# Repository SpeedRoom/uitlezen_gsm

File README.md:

Testcode voor het aansturen van de TFT dispalys die zullen dienen als gsm's.

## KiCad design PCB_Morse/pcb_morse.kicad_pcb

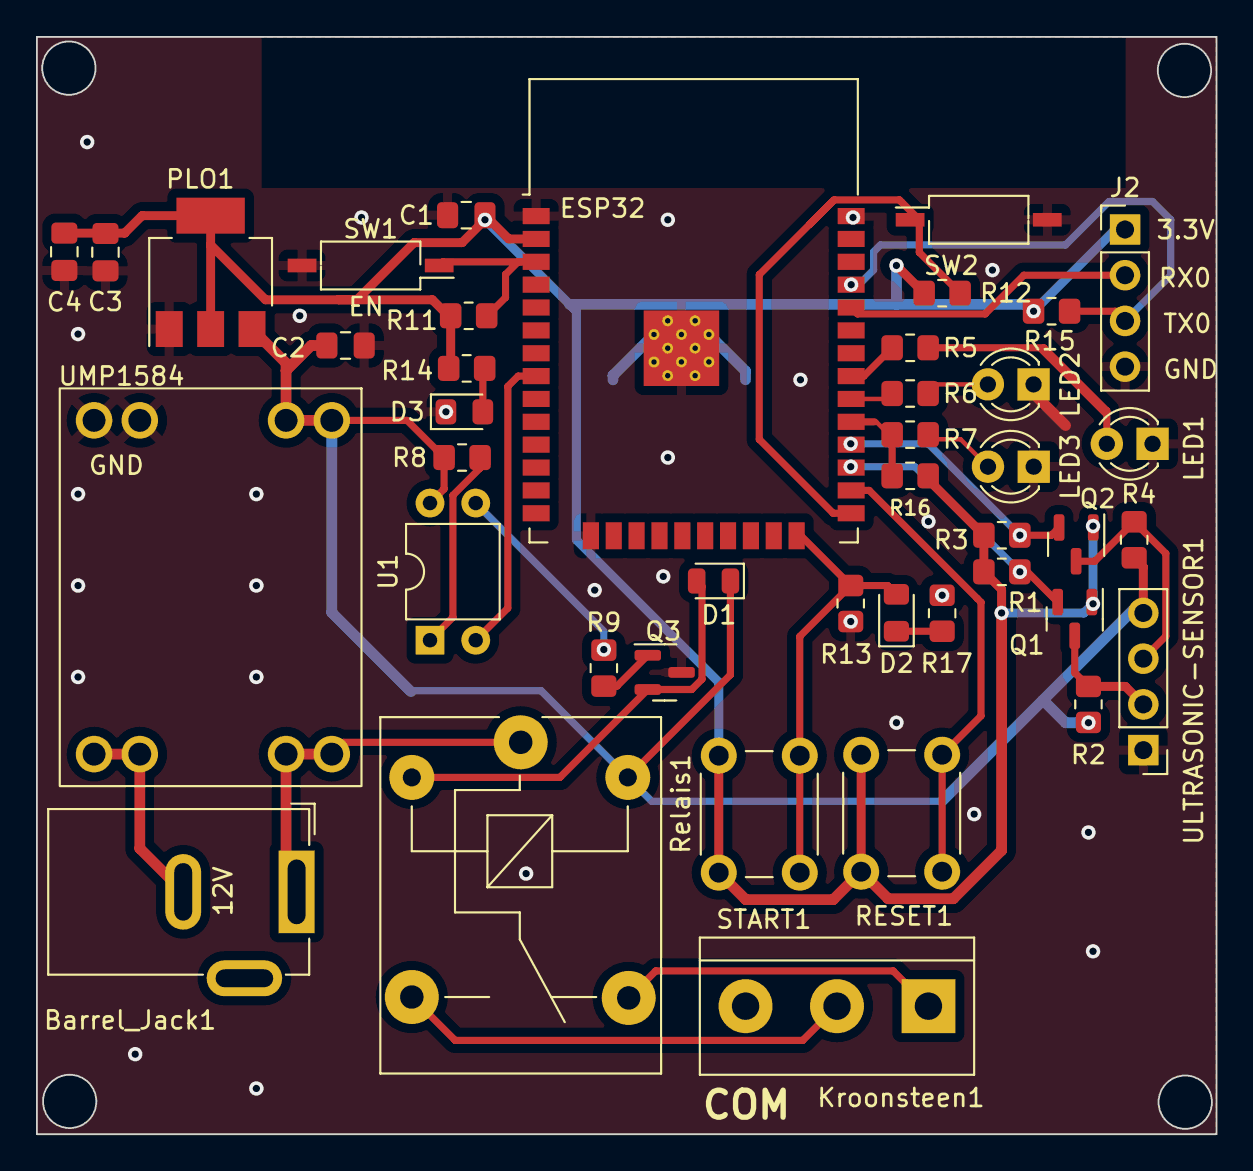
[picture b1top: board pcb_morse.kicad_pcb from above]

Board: 2 copper layers, 65.5 x 61.0 mm, 42 parts (0 on the bottom side), 30 nets.

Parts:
Barrel_Jack1: Barrel_Jack; BarrelJack_GCT_DCJ200-10-A_Horizontal
C1: 47uF/6.3V; C_0805_2012Metric_Pad1.18x1.45mm_HandSolder
C2, C4: 10uF; C_0805_2012Metric_Pad1.18x1.45mm_HandSolder
C3: 100nF; C_0805_2012Metric_Pad1.18x1.45mm_HandSolder
D1: 1n4148; D_0805_2012Metric
D2: BLUE; LED_0805_2012Metric_Pad1.15x1.40mm_HandSolder
D3: PWR; LED_0805_2012Metric_Pad1.15x1.40mm_HandSolder
ESP32: ESP32-WROOM-32
J2: Conn_01x04_Pin; PinHeader_1x04_P2.54mm_Vertical
Kroonsteen1: Screw_Terminal_01x03; TerminalBlock_bornier-3_P5.08mm
LED1: YELLOW; LED_D3.0mm
LED2: GREEN; LED_D3.0mm
LED3: RED; LED_D3.0mm
PLO1: AMS1117-3.3; SOT-223-3_TabPin2
Q1, Q2: BSS138; SOT-23
Q3: Q_NPN_BCE; SOT-23
R1, R2, R3, R4: 10k; R_0805_2012Metric_Pad1.20x1.40mm_HandSolder
R5, R6, R7: 270; R_0805_2012Metric_Pad1.20x1.40mm_HandSolder
R8, R9: 1k; R_0805_2012Metric_Pad1.20x1.40mm_HandSolder
R11, R12, R13, R15, R16: 10K; R_0805_2012Metric_Pad1.20x1.40mm_HandSolder
R14, R17: 1K; R_0805_2012Metric_Pad1.20x1.40mm_HandSolder
RESET1: SW_Push; SW_PUSH_6mm
Relais1: SANYOU_SRD_Form_C; Relay_SPDT_SANYOU_SRD_Series_Form_C
START1: SW_Push; SW_PUSH_6mm
SW1: EN; SW_DIP_SPSTx01_Slide_Copal_CHS-01B_W7.62mm_P1.27mm
SW2: FLASH; SW_DIP_SPSTx01_Slide_Copal_CHS-01B_W7.62mm_P1.27mm
U1: EL817; DIP-4_W7.62mm
ULTRASONIC-SENSOR1: Conn_01x04_Socket; PinHeader_1x04_P2.54mm_Vertical
UMP1584: MP1584; U1584

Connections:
+3.3V: C1.1, C3.2, C4.1, ESP32.2 (VDD), J2.1, PLO1.2 (VO), Q1.1 (G), Q2.1 (G), R1.1, R3.1, R11.1, R12.1, R14.1, R15.1, R16.1, RESET1.1 (1A), START1.1 (1A)
+12V: Barrel_Jack1.1, Relais1.1, UMP1584.3 (IN+), UMP1584.4 (IN+)
/EN: ESP32.3 (EN), R11.2, SW1.1
GND: C1.2, C2.2, C3.1, C4.2, D3.1 (K), ESP32.1 (GND), ESP32.15 (GND), ESP32.38 (GND), ESP32.39 (GND), J2.4, Kroonsteen1.3, LED1.1 (K), LED2.1 (K), LED3.1 (K), PLO1.1 (GND), Q3.3 (E), R13.1, R17.2, SW1.2, SW2.2, ULTRASONIC-SENSOR1.1, UMP1584.7 (OUT-), UMP1584.8 (OUT-)
GPIO0: ESP32.25 (IO0), R12.2, SW2.1
GPIO2: D2.2 (A), ESP32.24 (IO2), R13.2, START1.2 (2B)
GPIO4: ESP32.26 (IO4), RESET1.2 (2B)
GPIO5: ESP32.29 (IO5), R7.1, R16.2
GPIO16: ESP32.27 (IO16), Q1.2 (S), R1.2
GPIO16-5V: Q1.3 (D), R2.2, ULTRASONIC-SENSOR1.2
GPIO17: ESP32.28 (IO17), Q2.2 (S), R3.2
GPIO17-5V: Q2.3 (D), R4.2, ULTRASONIC-SENSOR1.3
GPIO18: ESP32.30 (IO18), R6.1
GPIO19: ESP32.31 (IO19), R5.1
GPIO32: ESP32.8 (IO32), U1.2
unnamed: Barrel_Jack1.2, UMP1584.1 (IN-), UMP1584.2 (IN-)
unnamed: D1.2 (A), Q3.2 (C), Relais1.2
unnamed: D2.1 (K), R17.1
unnamed: D3.2 (A), R14.2
unnamed: Kroonsteen1.1, Relais1.4
unnamed: Kroonsteen1.2, Relais1.3
unnamed: LED1.2 (A), R5.2
unnamed: LED2.2 (A), R6.2
unnamed: LED3.2 (A), R7.2
unnamed: Q3.1 (B), R9.2
unnamed: R8.2, U1.1
unnamed: R9.1, U1.3
RX0: ESP32.34 (RXD0/IO3), J2.2
TX0: ESP32.35 (TXD0/IO1), J2.3, R15.2
VDD: C2.1, D1.1 (K), PLO1.3 (VI), R2.1, R4.1, R8.1, Relais1.5, U1.4, ULTRASONIC-SENSOR1.4, UMP1584.5 (OUT+), UMP1584.6 (OUT+)

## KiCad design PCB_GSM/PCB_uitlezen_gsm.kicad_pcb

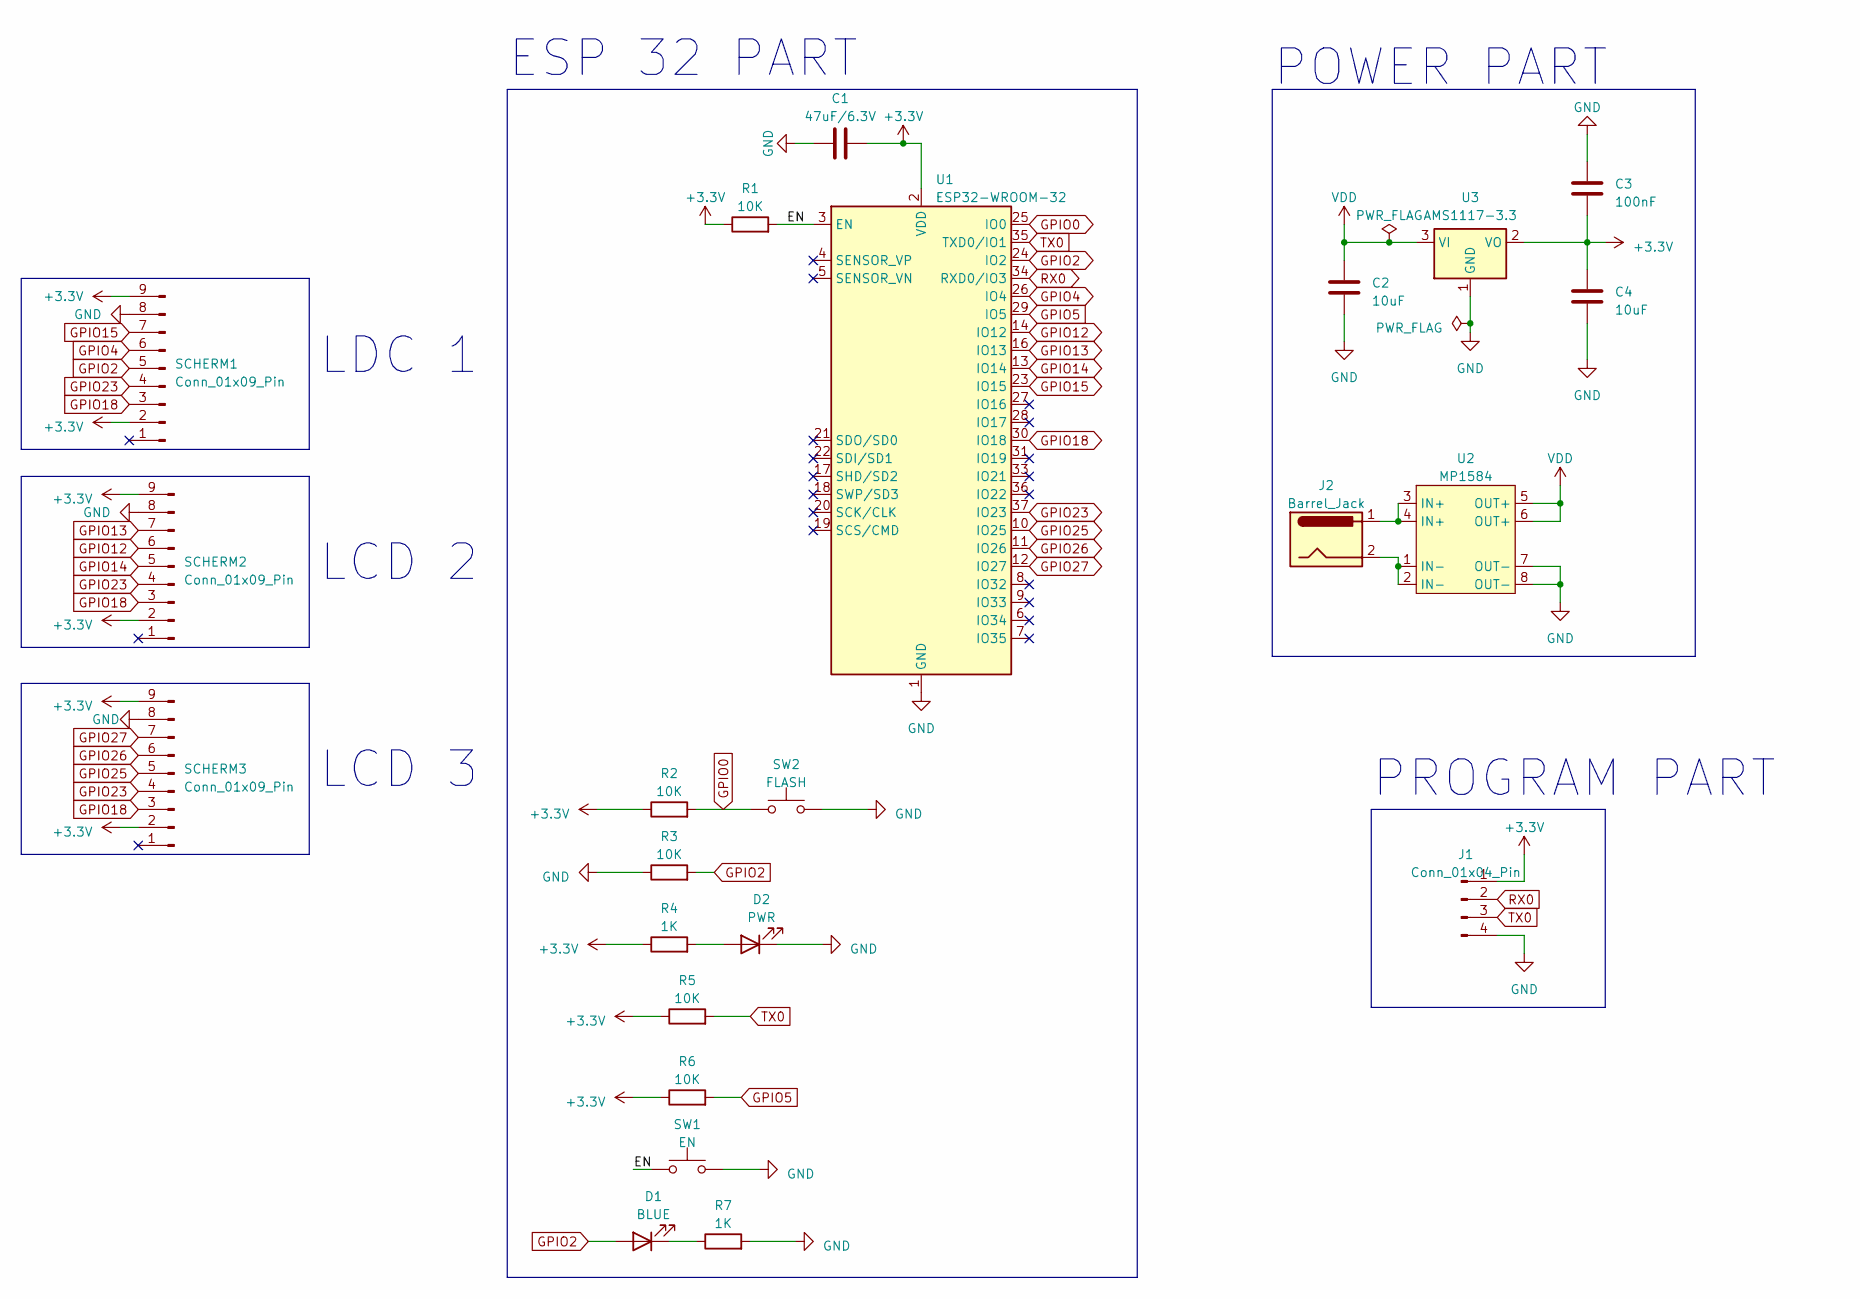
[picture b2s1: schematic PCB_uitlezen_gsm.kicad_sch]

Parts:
C1: 47uF/6.3V; C_0805_2012Metric_Pad1.18x1.45mm_HandSolder
C2, C4: 10uF; C_0805_2012Metric_Pad1.18x1.45mm_HandSolder
C3: 100nF; C_0805_2012Metric_Pad1.18x1.45mm_HandSolder
D1: BLUE; LED_0805_2012Metric_Pad1.15x1.40mm_HandSolder
D2: PWR; LED_0805_2012Metric_Pad1.15x1.40mm_HandSolder
J1: Conn_01x04_Pin; PinHeader_1x04_P2.54mm_Vertical
J2: Barrel_Jack; BarrelJack_GCT_DCJ200-10-A_Horizontal
R1, R2, R3, R5, R6: 10K; R_0805_2012Metric_Pad1.20x1.40mm_HandSolder
R4, R7: 1K; R_0805_2012Metric_Pad1.20x1.40mm_HandSolder
SCHERM1, SCHERM2, SCHERM3: Conn_01x09_Pin; PinHeader_1x09_P2.54mm_Vertical
SW1: EN; SW_DIP_SPSTx01_Slide_Copal_CHS-01B_W7.62mm_P1.27mm
SW2: FLASH; SW_DIP_SPSTx01_Slide_Copal_CHS-01B_W7.62mm_P1.27mm
U1: ESP32-WROOM-32
U2: MP1584; U1584
U3: AMS1117-3.3; SOT-223-3_TabPin2

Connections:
+3.3V: C1.1, C3.2, C4.1, J1.1, R1.1, R2.1, R4.1, R5.1, R6.1, SCHERM1.2, SCHERM1.9, SCHERM2.2, SCHERM2.9, SCHERM3.2, SCHERM3.9, U1.2 (VDD), U3.2 (VO)
/EN: R1.2, SW1.1, U1.3 (EN)
GND: C1.2, C2.2, C3.1, C4.2, D2.1 (K), J1.4, R3.1, R7.2, SCHERM1.8, SCHERM2.8, SCHERM3.8, SW1.2, SW2.2, U1.1 (GND), U1.15 (GND), U1.38 (GND), U1.39 (GND), U2.7 (OUT-), U2.8 (OUT-), U3.1 (GND)
GPIO0: R2.2, SW2.1, U1.25 (IO0)
GPIO2: D1.2 (A), R3.2, SCHERM1.5, U1.24 (IO2)
GPIO4: SCHERM1.6, U1.26 (IO4)
GPIO5: R6.2, U1.29 (IO5)
GPIO12: SCHERM2.6, U1.14 (IO12)
GPIO13: SCHERM2.7, U1.16 (IO13)
GPIO14: SCHERM2.5, U1.13 (IO14)
GPIO15: SCHERM1.7, U1.23 (IO15)
GPIO18: SCHERM1.3, SCHERM2.3, SCHERM3.3, U1.30 (IO18)
GPIO23: SCHERM1.4, SCHERM2.4, SCHERM3.4, U1.37 (IO23)
GPIO25: SCHERM3.5, U1.10 (IO25)
GPIO26: SCHERM3.6, U1.11 (IO26)
GPIO27: SCHERM3.7, U1.12 (IO27)
unnamed: D1.1 (K), R7.1
unnamed: D2.2 (A), R4.2
unnamed: J2.1, U2.3 (IN+), U2.4 (IN+)
unnamed: J2.2, U2.1 (IN-), U2.2 (IN-)
RX0: J1.2, U1.34 (RXD0/IO3)
TX0: J1.3, R5.2, U1.35 (TXD0/IO1)
VDD: C2.1, U2.5 (OUT+), U2.6 (OUT+), U3.3 (VI)

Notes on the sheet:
LCD 3
ESP 32 PART
LDC 1
PROGRAM PART
LCD 2
POWER PART

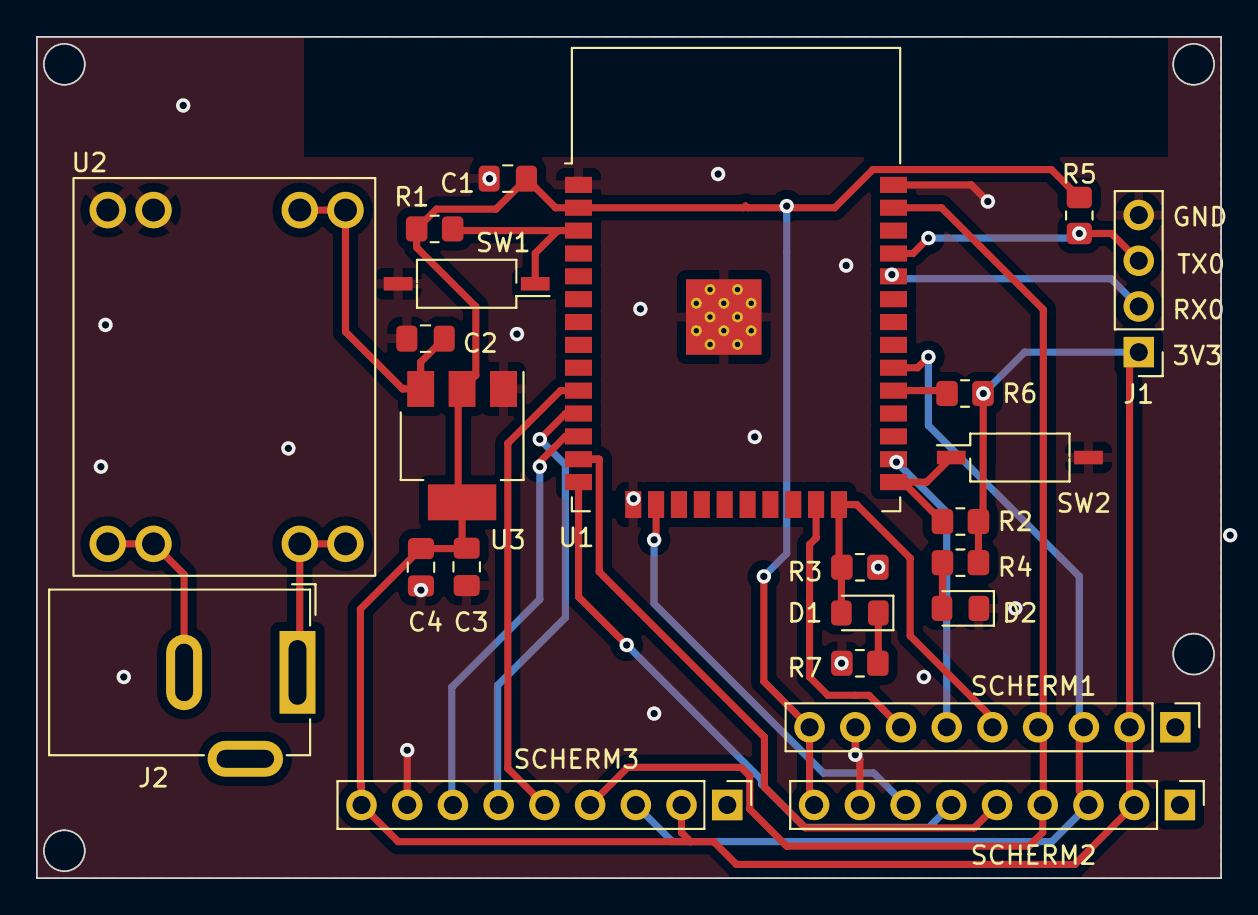
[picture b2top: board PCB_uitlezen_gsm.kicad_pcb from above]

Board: 2 copper layers, 65.8 x 46.7 mm, 23 parts (0 on the bottom side), 23 nets.

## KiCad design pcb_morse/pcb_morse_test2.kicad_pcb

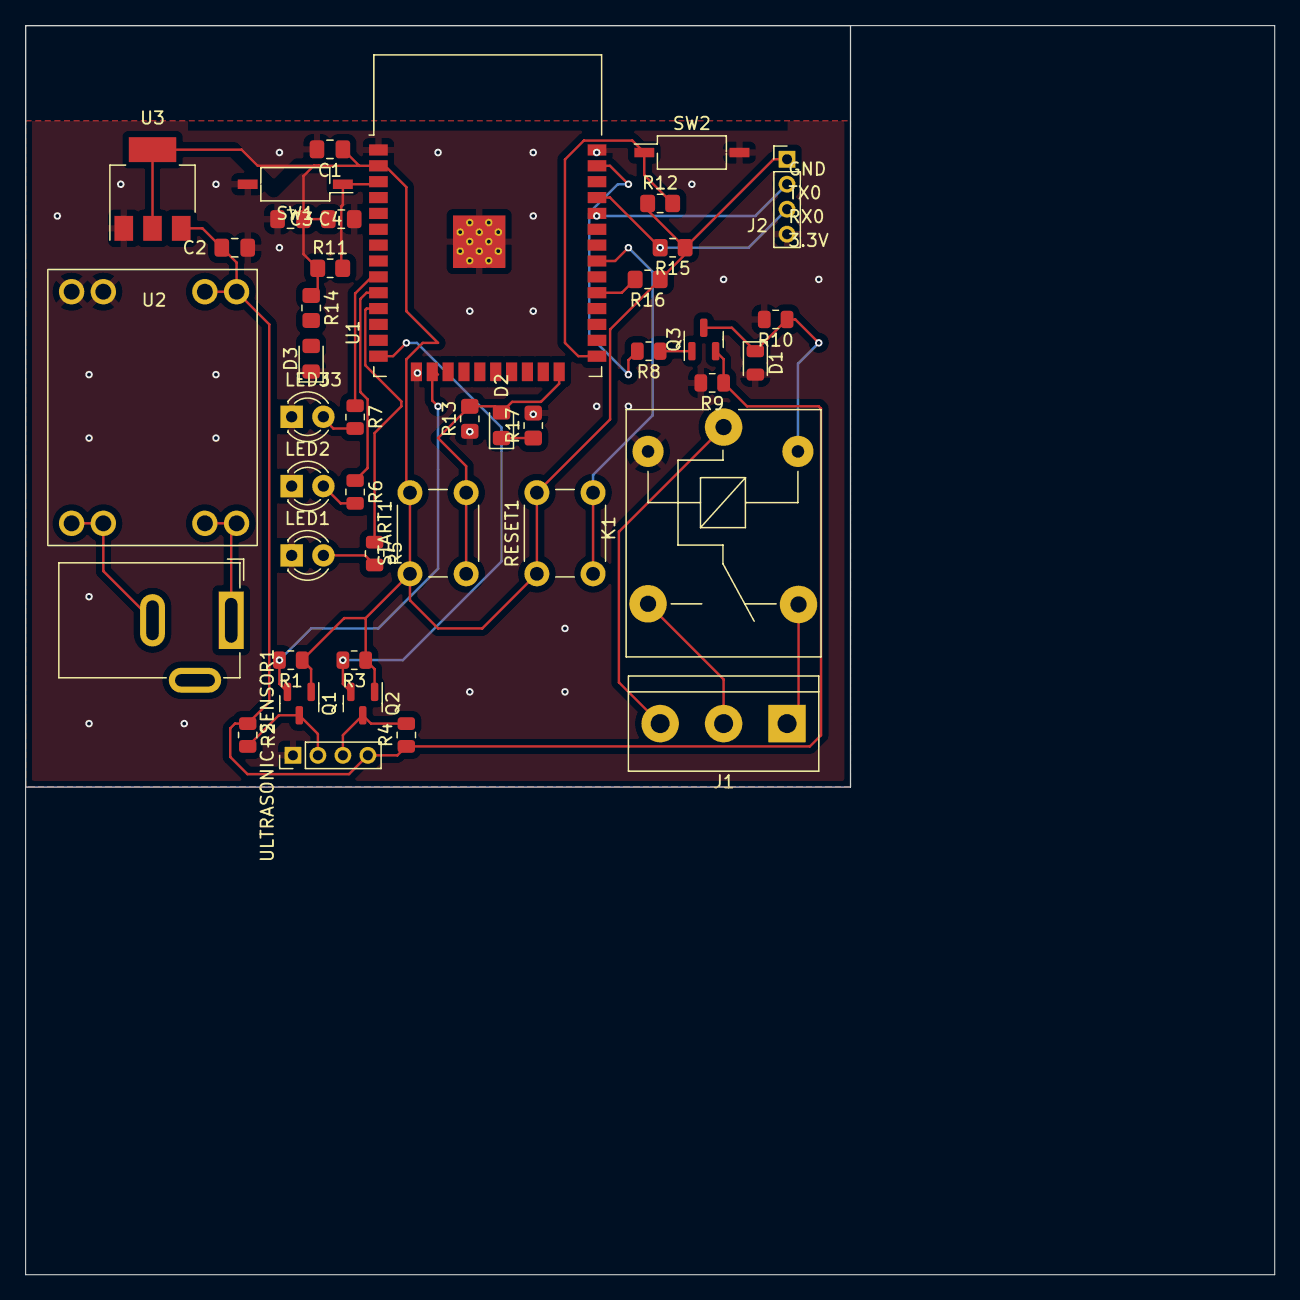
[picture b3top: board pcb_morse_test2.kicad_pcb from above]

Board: 2 copper layers, 100.0 x 100.0 mm, 42 parts (0 on the bottom side), 30 nets.

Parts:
C1: 100uF/6.3V; C_0805_2012Metric_Pad1.18x1.45mm_HandSolder
C2, C4: 10uF; C_0805_2012Metric_Pad1.18x1.45mm_HandSolder
C3: 100nF; C_0805_2012Metric_Pad1.18x1.45mm_HandSolder
D1: D; D_0805_2012Metric
D2: BLUE; LED_0805_2012Metric_Pad1.15x1.40mm_HandSolder
D3: PWR; LED_0805_2012Metric_Pad1.15x1.40mm_HandSolder
J1: Screw_Terminal_01x03; TerminalBlock_bornier-3_P5.08mm
J2: Conn_01x04_Pin; PinHeader_1x04_P2.00mm_Vertical
J3: Barrel_Jack; BarrelJack_GCT_DCJ200-10-A_Horizontal
K1: SANYOU_SRD_Form_C; Relay_SPDT_SANYOU_SRD_Series_Form_C
LED1: YELLOW; LED_D3.0mm
LED2: GREEN; LED_D3.0mm
LED3: RED; LED_D3.0mm
Q1, Q2: BSS138; SOT-23
Q3: MMBT3906; SOT-23
R1, R2, R3, R4: 10k; R_0805_2012Metric
R5, R6, R7: 270; R_0805_2012Metric
R8, R9, R10: 1k; R_0805_2012Metric
R11, R12, R13, R15, R16: 10K; R_0805_2012Metric_Pad1.20x1.40mm_HandSolder
R14, R17: 1K; R_0805_2012Metric_Pad1.20x1.40mm_HandSolder
RESET1: SW_Push; SW_PUSH_6mm
START1: SW_Push; SW_PUSH_6mm
SW1: EN; SW_DIP_SPSTx01_Slide_Copal_CHS-01B_W7.62mm_P1.27mm
SW2: FLASH; SW_DIP_SPSTx01_Slide_Copal_CHS-01B_W7.62mm_P1.27mm
U1: ESP32-WROOM-32
U2: MP1584; U1584
U3: AMS1117-3.3; SOT-223-3_TabPin2
ULTRASONIC-SENSOR1: Conn_01x04_Socket; PinHeader_1x04_P2.00mm_Vertical

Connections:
+3.3V: C1.1, C3.2, C4.1, J2.1, Q1.1 (G), Q2.1 (G), R1.1, R3.1, R11.1, R12.1, R14.1, R15.1, R16.1, RESET1.1 (1B), START1.1 (1A), U1.2 (VDD), U3.2 (VO)
/EN: R11.2, SW1.1, U1.3 (EN)
GND: C1.2, C2.2, C3.1, C4.2, D1.2 (A), D3.1 (K), J2.4, K1.2, LED1.1 (K), LED2.1 (K), LED3.1 (K), R9.2, R10.2, R13.1, R17.2, SW1.2, SW2.2, U1.1 (GND), U1.15 (GND), U1.38 (GND), U1.39 (GND), U2.7 (OUT-), U2.8 (OUT-), U3.1 (GND), ULTRASONIC-SENSOR1.1
GPIO0: R12.2, SW2.1, U1.25 (IO0)
GPIO2: D2.2 (A), R13.2, START1.2 (2B), U1.24 (IO2)
GPIO5: R16.2, U1.29 (IO5)
GPIO12: Q2.2 (S), R3.2, U1.14 (IO12)
GPIO12-5V: Q2.3 (D), R4.2, ULTRASONIC-SENSOR1.3
GPIO13: Q1.2 (S), R1.2, U1.16 (IO13)
GPIO13-5V: Q1.3 (D), R2.2, ULTRASONIC-SENSOR1.2
GPIO19: RESET1.2 (2B), U1.31 (IO19)
GPIO23: R8.2, U1.37 (IO23)
GPIO25: R6.1, U1.10 (IO25)
GPIO26: R5.1, U1.11 (IO26)
GPIO33: R7.1, U1.9 (IO33)
unnamed: D1.1 (K), K1.5, Q3.3 (C), R10.1
unnamed: D2.1 (K), R17.1
unnamed: D3.2 (A), R14.2
unnamed: J1.1, K1.4
unnamed: J1.2, K1.3
unnamed: J1.3, K1.1
unnamed: J3.1, U2.3 (IN+), U2.4 (IN+)
unnamed: J3.2, U2.1 (IN-), U2.2 (IN-)
unnamed: LED1.2 (A), R5.2
unnamed: LED2.2 (A), R6.2
unnamed: LED3.2 (A), R7.2
unnamed: Q3.1 (B), R8.1
RX0: J2.2, U1.34 (RXD0/IO3)
TX0: J2.3, R15.2, U1.35 (TXD0/IO1)
VDD: C2.1, Q3.2 (E), R2.1, R4.1, R9.1, U2.5 (OUT+), U2.6 (OUT+), U3.3 (VI), ULTRASONIC-SENSOR1.4

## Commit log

2023-02-23 test display toevoegen
2023-02-23 test ultrasonic sensor code
2023-02-28 final version
2023-03-28 OTA added
2023-03-28 OTA updated
2023-03-28 upload code
2023-03-28 UPDATE PCB MORSE
2023-03-28 UPDATE PCB UITLEZEN GSM
2023-03-28 Clean PCB design uitlezen gsm
2023-03-28 clean PCB design morse code
2023-04-19 update pcb design 2
2023-04-19 update pcb uitlezen gsm design 2
2023-05-02 clean up
2023-05-08 3d print
2023-05-08 lasercut box
2023-05-09 mqtt
2023-05-09 update 3d print
2023-05-09 update MQTT
2023-05-10 update code
2023-05-10 update ota
2023-05-11 update ota code
2023-05-11 update code gsm + 3d print button
2023-05-14 update main
2023-05-14 csv file
2023-05-14 update csv
2023-05-16 delete
